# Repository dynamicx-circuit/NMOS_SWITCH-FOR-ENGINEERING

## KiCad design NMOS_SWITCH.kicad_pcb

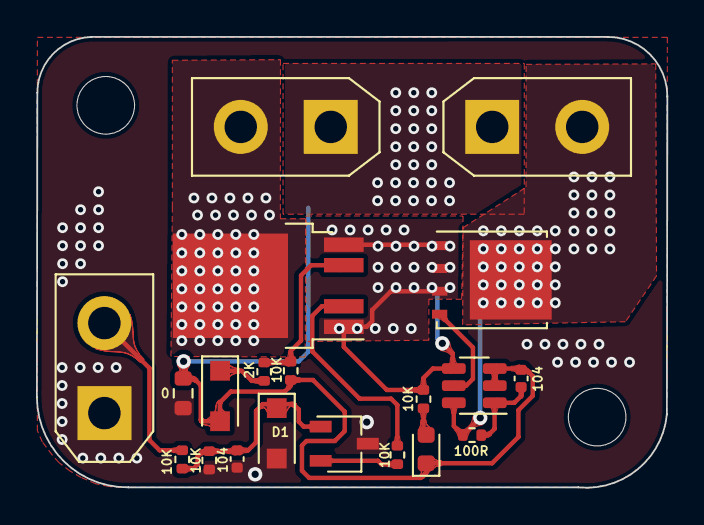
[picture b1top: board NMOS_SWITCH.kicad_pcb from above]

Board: 2 copper layers, 35.0 x 25.0 mm, 22 parts (0 on the bottom side), 14 nets.

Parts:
0: 0; R_0603_1608Metric
2K: 2k; R_0402_1005Metric
10K, 10K#2, 10K#3, 10K#4, 10K#5: 10k; R_0402_1005Metric
100R: 100R; R_0402_1005Metric
104, 104#2: 104; C_0402_1005Metric
D1, D2: BZT52Bxx; D_SOD-123F
D3: LED; LED_0603_1608Metric
H1, H2: MountingHole; MountingHole_3.2mm_M3
J1, J2, J3: Conn_01x02; AMASS_XT30UPB-M_1x02_P5.0mm_Vertical
Q1: Q_NPN_BCE; TSOT-23
Q2: CSD18540Q5B; TDSON-8-1
U1: BTS443P; TO-252-4
U2: LM5050-1; TSOT-23-6

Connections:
/EN: 10K#2.1, J1.2
/NMOS_IN: J2.2, U1.3 (Vbb)
/NMOS_OUT: 100R.1, J3.2, Q2.5 (D), U2.6 (OUT)
GND: 0.1, 10K#5.2, 104.2, D1.2 (A), J1.1, Q1.3 (E)
GNDPWR: 0.2, 10K#3.1, 104#2.2, D2.2 (A), D3.1 (K), J2.1, J3.1, U2.2 (GND), U2.3 (OFF)
unnamed: 10K#2.2, 10K#5.1, 104.1, D1.1 (K), Q1.1 (B)
unnamed: 100R.2, 104#2.1, U2.1 (VS)
unnamed: 2K.2, D2.1 (K)
unnamed: 10K#4.2, D3.2 (A)
unnamed: 10K.1, Q1.2 (C)
unnamed: 10K#4.1, Q2.1 (S), Q2.2 (S), Q2.3 (S), U1.1 (OUT), U1.5 (OUT), U2.4 (IN)
unnamed: Q2.4 (G), U2.5 (GATE)
unnamed: 10K.2, U1.2 (IN)
unnamed: 2K.1, 10K#3.2, U1.4 (IS)

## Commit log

2022-09-02 Transplant NMOS switch from AD to Kicad
2022-10-24 Adoption changes for engineering
2022-10-27 Add mask
2022-11-02 Change some footprints
